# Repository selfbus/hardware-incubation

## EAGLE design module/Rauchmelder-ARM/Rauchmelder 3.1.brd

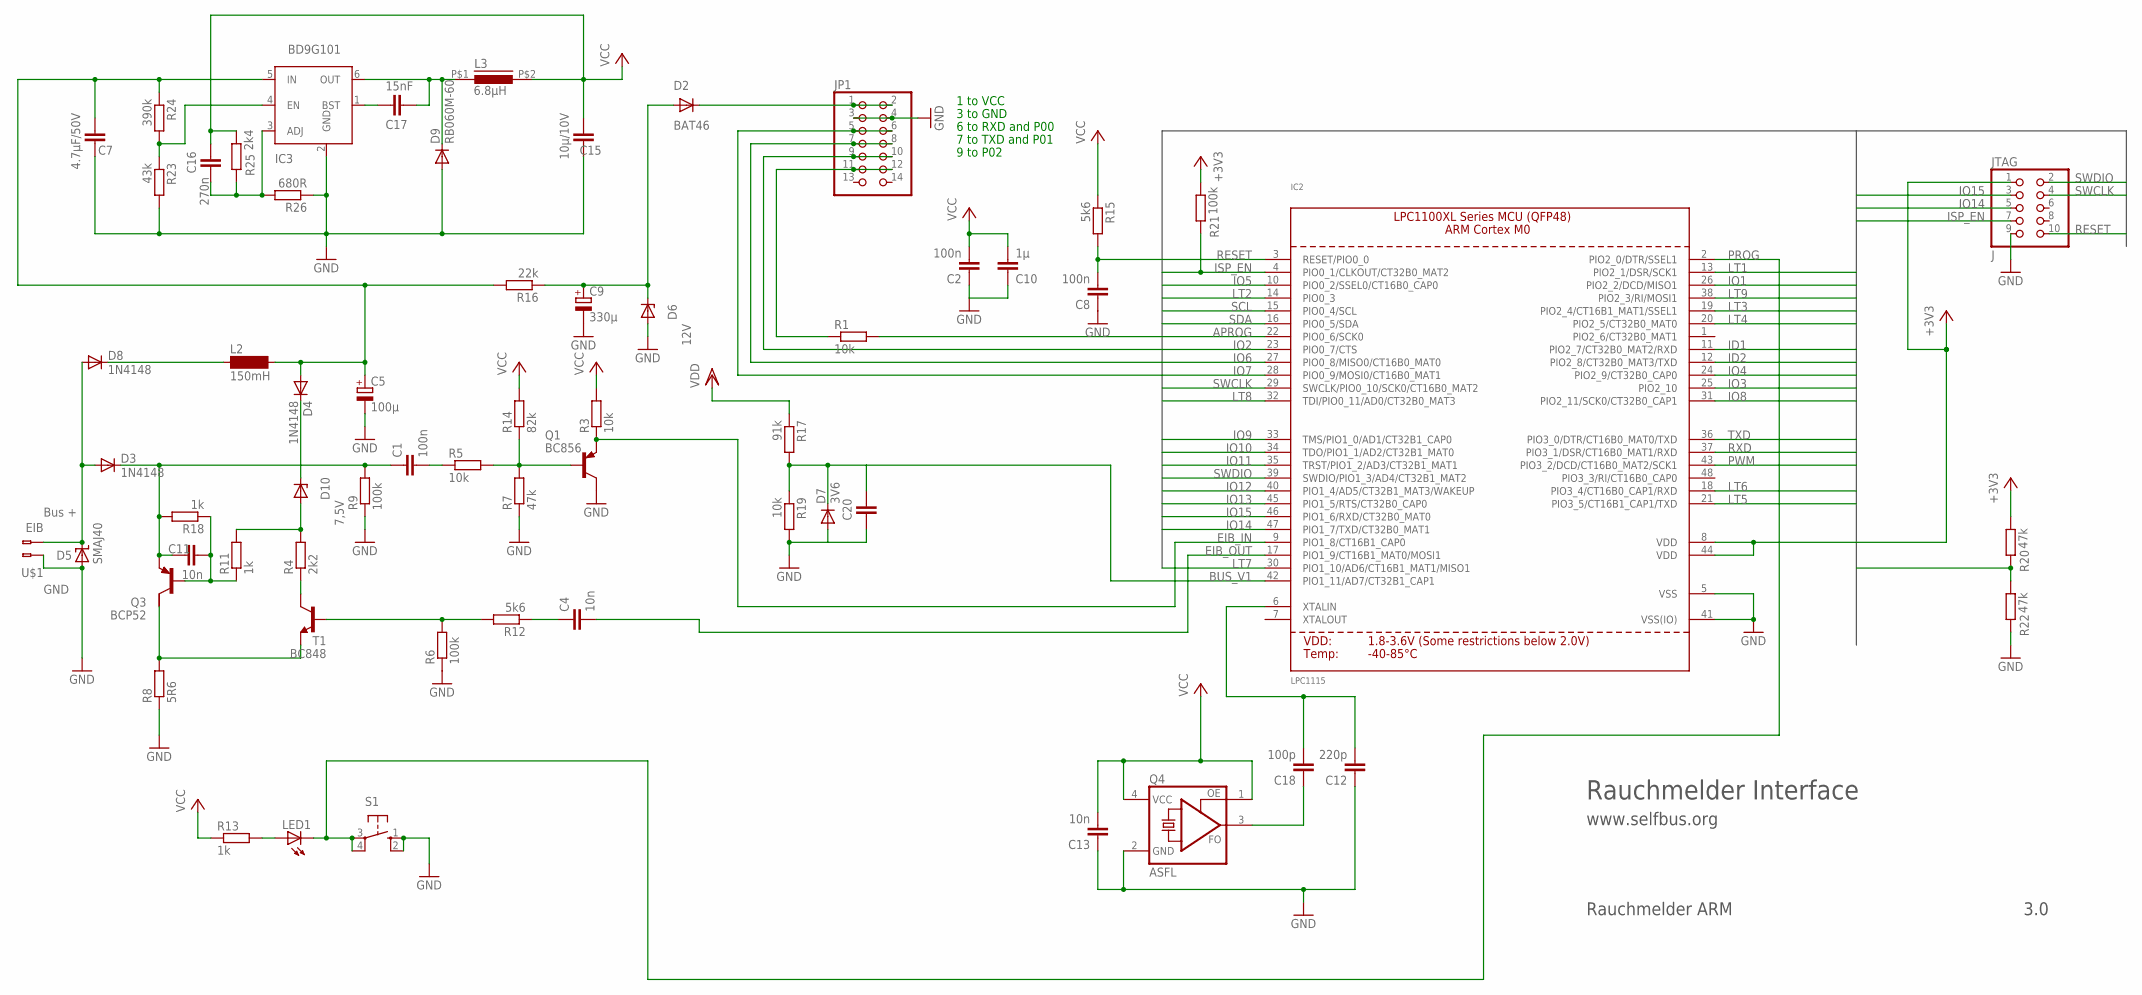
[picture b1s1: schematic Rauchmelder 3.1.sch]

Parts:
C1, C2, C8: 100n; C1206
C4, C11, C13: 10n; C1206
C5: 100µ; SANYO-OSCON_SMD_C6
C7: 4.7µF/50V; C1206K
C9: 330µ; E3,5-8
C10: 1µ; C1206
C12: 220p; C1206
C15: 10µ/10V; C1206K
C16: 270n; C1206
C17: 15nF; C1206
C18: 100p; C1206
C20: C-EUC1206; C1206
D2: BAT46; MINIMELF
D3, D4, D8: 1N4148; MINIMELF
D5: SMAJ40; SMBJ
D6: 12V; MINIMELF
D7: 3V6; MINIMELF
D9: RB060M-60; SOD123
D10: 7,5V; MINIMELF
IC2: LPC1115; LQFP48
IC3: BD9G101; SOT23-6
JP1: PINHD-2X7; 2X07
JTAG: J; 2X05M
L2: 150mH; BS11
L3: 6.8µH; PIS2812
LED1: LED3MM
Q1: BC856; SOT23-BEC
Q3: BCP52; SOT223
Q4: ASFL; ASF
R1, R3, R5, R19: 10k; R1206
R4: 2k2; R1206
R6, R9, R21: 100k; R1206
R7, R20, R22: 47k; R1206
R8: 5R6; R1206
R11, R13, R18: 1k; R1206
R12, R15: 5k6; R1206
R14: 82k; R1206
R16: 22k; R1206
R17: 91k; R1206
R23: 43k; R1206
R24: 390k; R1206
R25: 2k4; R1206
R26: 680R; R1206
S1: 10-XX; B3F-10XX
T1: BC848; SOT23
U$1: EIB; BUSKLEMME243-724

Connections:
ADJ: C16.1, IC3.3 (ADJ), R25.1, R26.2
APROG: IC2.22 (PIO0_6/SCK0)
BUS_V1: C20.2, D7.C, IC2.42 (PIO1_11/AD7/CT32B1_CAP1), R17.2, R19.1
EIB+: D3.A, D5.C, D8.A, U$1.2 (B-2)
EIB_DC: C5.+, C7.2, D4.A, IC3.5 (IN), L2.2, R16.2, R17.1, R24.1
EIB_IN: IC2.9 (PIO1_8/CT16B1_CAP0), Q1.E, R3.1
EIB_OUT: C4.2, IC2.17 (PIO1_9/CT16B1_MAT0/MOSI1)
ENABLE_SW: IC3.4 (EN), R23.1, R24.2
GND: C2.1, C5.-, C7.1, C8.1, C9.-, C10.1, C12.1, C13.1, C15.1, C20.1, D5.A, D6.A, D7.A, D9.A, IC2.5 (VSS), IC2.41 (VSS(IO)), IC3.2 (GND), JP1.3, JP1.4, JTAG.9, Q1.C, Q4.2 (GND), R6.1, R7.1, R8.1, R9.1, R19.2, R22.1, R23.2, R26.1, S1.1 (S), S1.2 (S1), U$1.1 (B-1)
ID1: IC2.11 (PIO2_7/CT32B0_MAT2/RXD)
ID2: IC2.12 (PIO2_8/CT32B0_MAT3/TXD)
IO1: IC2.26 (PIO2_2/DCD/MISO1)
IO2: IC2.23 (PIO0_7/CTS)
IO3: IC2.25 (PIO2_10)
IO4: IC2.24 (PIO2_9/CT32B0_CAP0)
IO5: IC2.10 (PIO0_2/SSEL0/CT16B0_CAP0)
IO6: IC2.27 (PIO0_8/MISO0/CT16B0_MAT0)
IO7: IC2.28 (PIO0_9/MOSI0/CT16B0_MAT1)
IO8: IC2.31 (PIO2_11/SCK0/CT32B0_CAP1)
IO9: IC2.33 (TMS/PIO1_0/AD1/CT32B1_CAP0)
IO10: IC2.34 (TDO/PIO1_1/AD2/CT32B1_MAT0)
IO11: IC2.35 (TRST/PIO1_2/AD3/CT32B1_MAT1)
IO12: IC2.40 (PIO1_4/AD5/CT32B1_MAT3/WAKEUP), R20.1, R22.2
IO13: IC2.45 (PIO1_5/RTS/CT32B0_CAP0)
IO14: IC2.47 (PIO1_7/TXD/CT32B0_MAT1), JTAG.5
IO15: IC2.46 (PIO1_6/RXD/CT32B0_MAT0), JTAG.3
ISP_EN: IC2.4 (PIO0_1/CLKOUT/CT32B0_MAT2), JTAG.7, R21.1
LT1: IC2.13 (PIO2_1/DSR/SCK1)
LT2: IC2.14 (PIO0_3)
LT3: IC2.19 (PIO2_4/CT16B1_MAT1/SSEL1)
LT4: IC2.20 (PIO2_5/CT32B0_MAT0)
LT5: IC2.21 (PIO3_5/CT16B1_CAP1/TXD), JP1.9, JP1.10
LT6: IC2.18 (PIO3_4/CT16B0_CAP1/RXD)
LT7: IC2.30 (PIO1_10/AD6/CT16B1_MAT1/MISO1)
LT8: IC2.32 (TDI/PIO0_11/AD0/CT32B0_MAT3), R1.2
LT9: IC2.38 (PIO2_3/RI/MOSI1)
LX: C17.1, D9.C, IC3.6 (OUT), L3.P$1 (1)
unnamed: JP1.11, JP1.12, R1.1
unnamed: Q1.B, R5.2, R7.2, R14.1
unnamed: C11.2, Q3.1 (B), R11.1, R18.1
unnamed: LED1.A, R13.2
unnamed: C9.+, D2.A, D6.C, R16.1
unnamed: D8.C, L2.1
unnamed: D4.C, D10.C
unnamed: C1.2, R5.1
unnamed: D2.C, JP1.1, JP1.2
unnamed: C17.2, IC3.1 (BST)
unnamed: C4.1, R12.1
unnamed: R4.1, T1.3 (C)
unnamed: D10.A, R4.2, R11.2
unnamed: Q3.2 (C), R8.2, T1.2 (E)
unnamed: C12.2, C18.2, IC2.6 (XTALIN)
unnamed: C1.1, C11.1, D3.C, Q3.3 (E), R9.2, R18.2
unnamed: R6.2, R12.2, T1.1 (B)
unnamed: C18.1, Q4.3 (FO)
PROG: IC2.2 (PIO2_0/DTR/SSEL1), LED1.K (C), S1.3, S1.4 (P1)
PWM: IC2.43 (PIO3_2/DCD/CT16B0_MAT2/SCK1)
RESET: C8.2, IC2.3 (RESET/PIO0_0), JTAG.10, R15.2
RXD: IC2.37 (PIO3_1/DSR/CT16B0_MAT1/RXD), JP1.5, JP1.6
SCL: IC2.15 (PIO0_4/SCL)
SDA: IC2.16 (PIO0_5/SDA)
SWCLK: IC2.29 (SWCLK/PIO0_10/SCK0/CT16B0_MAT2), JTAG.4
SWDIO: IC2.39 (SWDIO/PIO1_3/AD4/CT32B1_MAT2), JTAG.2
TXD: IC2.36 (PIO3_0/DTR/CT16B0_MAT0/TXD), JP1.7, JP1.8
VCC: C2.2, C10.2, C13.2, C15.2, C16.2, IC2.8 (VDD), IC2.44 (VDD), JTAG.1, L3.P$2 (2), Q4.1 (OE), Q4.4 (VCC), R3.2, R13.1, R14.2, R15.1, R20.2, R21.2, R25.2

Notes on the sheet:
Bus +
GND
Rauchmelder Interface
www.selfbus.org
Rauchmelder ARM
3.0
6 to RXD and P00
7 to TXD and P01
9 to P02
1 to VCC
3 to GND

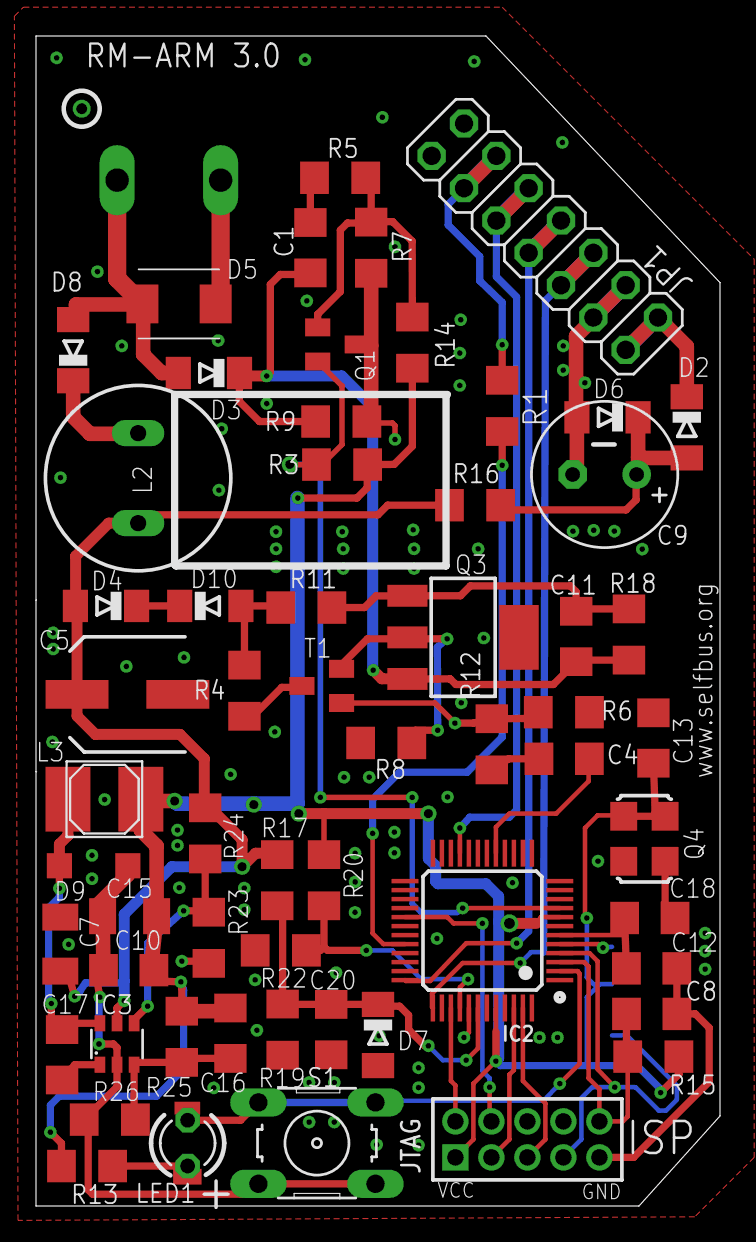
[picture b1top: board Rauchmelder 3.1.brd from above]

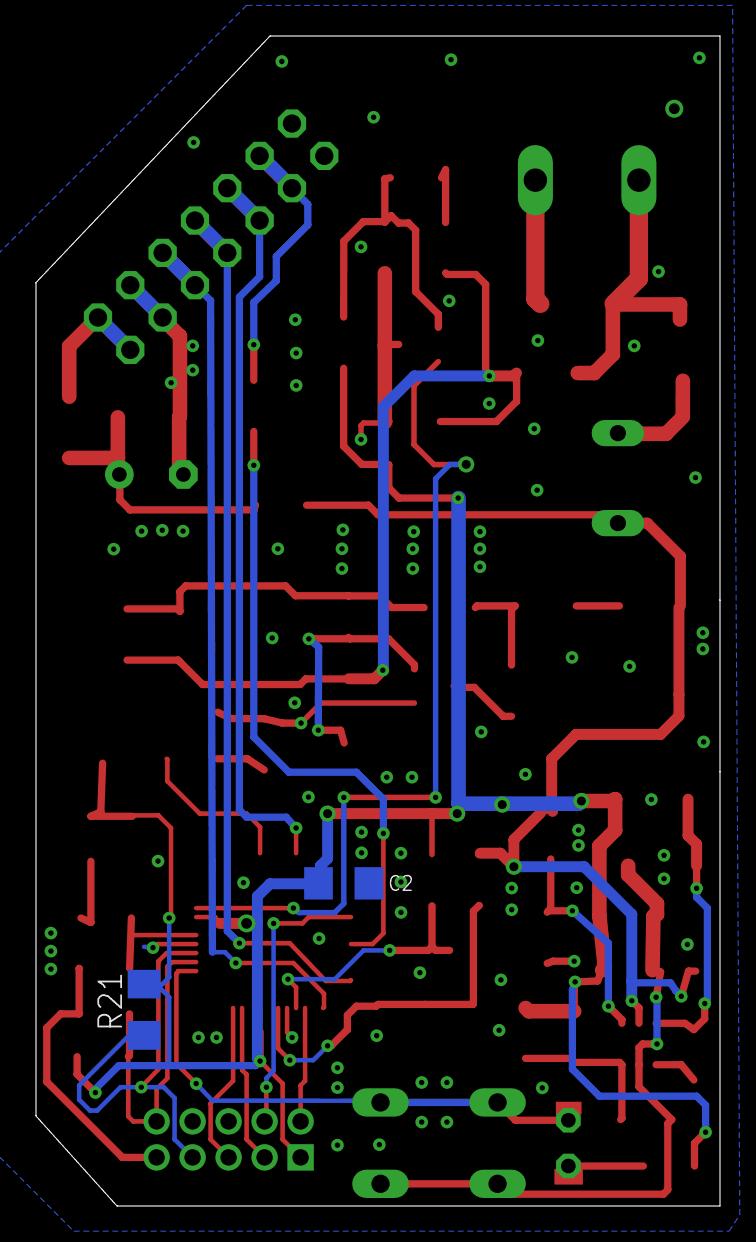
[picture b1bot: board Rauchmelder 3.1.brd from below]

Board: 2 copper layers, 38.0 x 65.0 mm, 62 parts (2 on the bottom side), 40 nets.

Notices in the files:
parts and their libraries:
microbuilder: This work is placed in the public domain, and may be freely used for commercial and non-commercial work with the following conditions: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
